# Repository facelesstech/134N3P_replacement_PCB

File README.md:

# 134N3P_replacement_PCB
134N3P_replacement_PCB

Items you will need.
   * [6 pin USB C Port](https://www.aliexpress.com/item/32966491026.html?spm=a2g0o.productlist.0.0.40682b02dGnW8h&algo_pvid=d52f6c09-77d8-4ea5-9f91-3c1a38f8a389&algo_exp_id=d52f6c09-77d8-4ea5-9f91-3c1a38f8a389-0&pdp_ext_f=%7B%22sku_id%22%3A%2266546029161%22%7D&pdp_npi=2%40dis%21GBP%21%210.47%210.47%21%211.97%21%21%402100bdd716543375023874249e4539%2166546029161%21sea)
   * [5.1k 0603 SMD resistors x2](https://www.aliexpress.com/item/1005001436923851.html?spm=a2g0o.productlist.0.0.1dab6ecdFCRr6p&algo_pvid=8ccb23e2-83dc-4ed7-917b-6b67ea6ceffa&algo_exp_id=8ccb23e2-83dc-4ed7-917b-6b67ea6ceffa-0&pdp_ext_f=%7B%22sku_id%22%3A%2212000016109475033%22%7D&pdp_npi=2%40dis%21GBP%21%210.09%210.09%21%21%21%21%402100bde316543376141027916e302a%2112000016109475033%21sea)
   * [134N3P Board](https://www.aliexpress.com/item/1005005373171153.html?spm=a2g0o.productlist.main.1.17bd75b9qR06g5&algo_pvid=98c39c75-c6d4-4cc3-a878-e4860ff9c67a&algo_exp_id=98c39c75-c6d4-4cc3-a878-e4860ff9c67a-0&pdp_npi=4%40dis%21GBP%210.99%210.87%21%21%211.22%21%21%40211b88ef16921774205801238edab4%2112000032789554978%21sea%21UK%21181881572%21&curPageLogUid=pOoZ8WYhE97o)

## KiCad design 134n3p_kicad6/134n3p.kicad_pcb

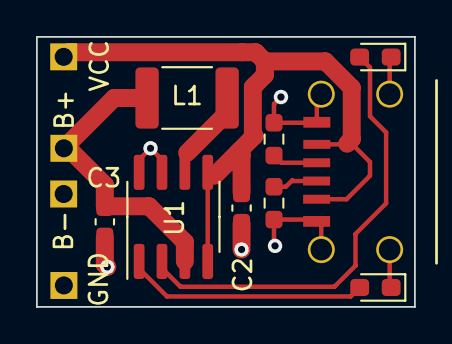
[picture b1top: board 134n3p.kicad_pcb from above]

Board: 2 copper layers, 21.0 x 15.0 mm, 13 parts (0 on the bottom side), 8 nets.

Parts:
B+: B+; 1mm_test_point_square
B-: B-; 1mm_test_point_square
BLUE: LED; LED_0603_1608Metric_Pad1.05x0.95mm_HandSolder
C2, C3: C; C_0603_1608Metric_Pad1.08x0.95mm_HandSolder
GND: GND; 1mm_test_point_square
L1: L 4.7uH; L_1812_4532Metric_Pad1.30x3.40mm_HandSolder
R1, R2: R; R_0603_1608Metric_Pad0.98x0.95mm_HandSolder
RED: LED; LED_0603_1608Metric_Pad1.05x0.95mm_HandSolder
U1: 134n3p; SOIC-8_3.9x4.9mm_P1.27mm
U2: usb_c_6pin; USB_C_6PIN_custom
VCC: VCC; 1mm_test_point_square

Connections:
GND: B-.1, BLUE.1 (K), C2.1, C3.2, GND.1, R1.1, R2.1, RED.1 (K), U1.7 (PGND), U1.8 (AGND), U2.1 (GND)
unnamed: C2.2, U1.4 (VOUT), U1.5 (VO/IN), U2.2 (VBUS), VCC.1
unnamed: B+.1, C3.1, L1.1, U1.3 (BTP)
unnamed: BLUE.2 (A), U1.2 (L2)
unnamed: RED.2 (A), U1.1 (L1)
unnamed: L1.2, U1.6 (LX)
unnamed: R1.2, U2.3 (CC2)
unnamed: R2.2, U2.4 (CC1)

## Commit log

2023-08-16 added kicad files
2023-08-16 added parts list
2023-08-16 fixed the link
2023-08-16 added 134n3p link
